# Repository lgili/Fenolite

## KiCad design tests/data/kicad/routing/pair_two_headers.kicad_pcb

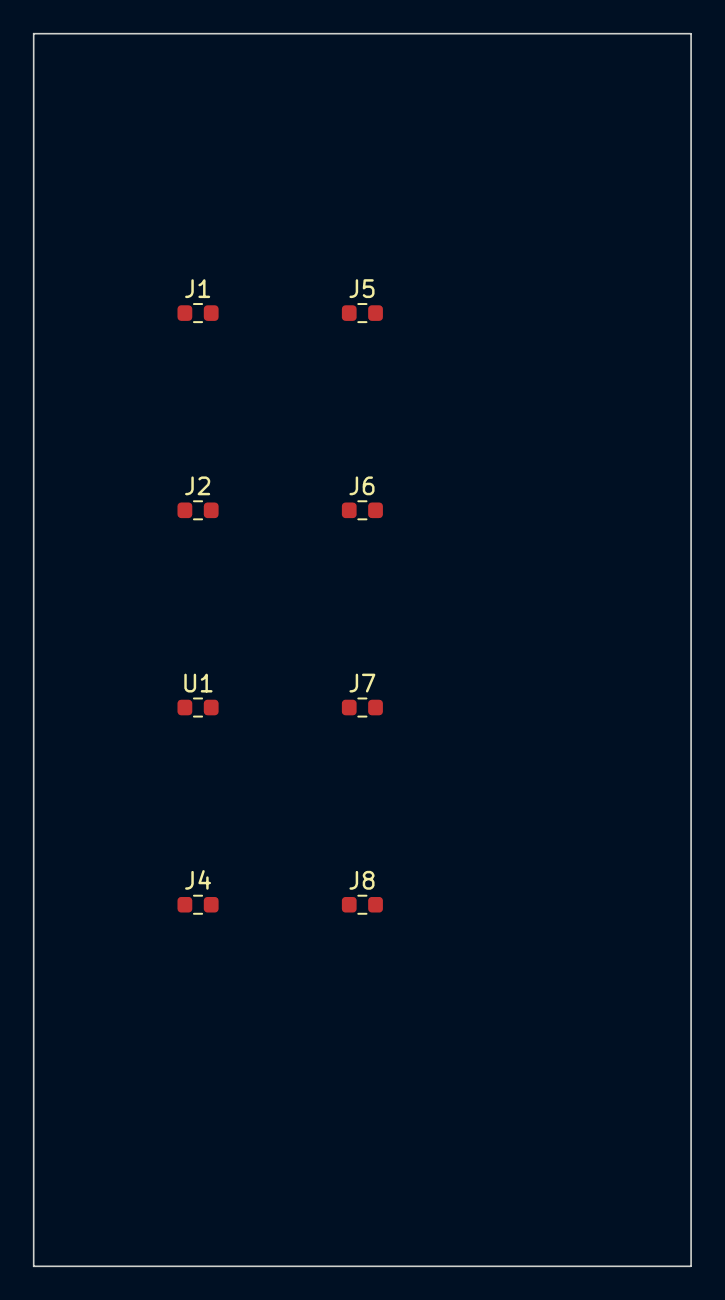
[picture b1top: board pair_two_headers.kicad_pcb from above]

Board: 2 copper layers, 40.0 x 75.0 mm, 8 parts (0 on the bottom side), 4 nets, no tracks yet.

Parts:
J1, J2, J4, J5, J6, J7, J8: Mini_R_0603
U1: Mini_R_0603

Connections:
S1: J7.1, U1.1
S2: J4.1, J8.1
USB_N: J2.1, J6.1
USB_P: J1.1, J5.1

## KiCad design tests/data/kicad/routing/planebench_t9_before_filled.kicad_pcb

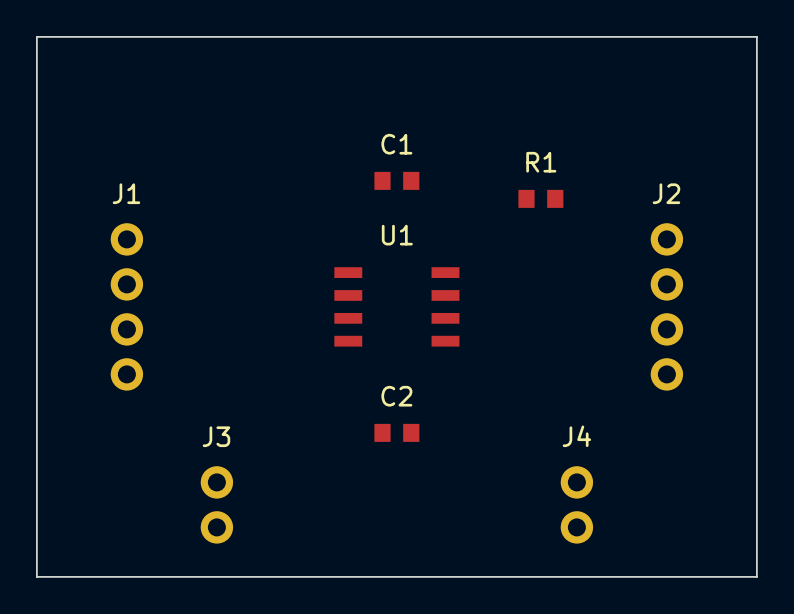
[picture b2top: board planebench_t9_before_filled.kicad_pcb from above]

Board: 4 copper layers, 40.0 x 30.0 mm, 8 parts (0 on the bottom side), 10 nets, no tracks yet.

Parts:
C1, C2: 100n; Chip_0603
J1: IN; Header_1x4_P2.5
J2: OUT; Header_1x4_P2.5
J3, J4: HV; Header_1x2_P2.5
R1: 1k; Chip_0603
U1: MCU; SOIC_8

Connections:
GND: C1.2, C2.2, J1.2, J2.3, U1.4
HV1: J3.1, J4.1
HV2: J3.2, J4.2
SIG1: J1.3, U1.1
SIG2: J1.4, U1.2
SIG3: R1.1, U1.3
SIG4: R1.2, U1.5
SIG5: J2.1, U1.6
SIG6: J2.2, U1.7
VCC: C1.1, C2.1, J1.1, J2.4, U1.8
